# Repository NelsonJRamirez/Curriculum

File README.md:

PROYECTOS MECÁNICOS, ESTRUCTURALES Y ELECTRÓNICOS DESTACADOS

Esta carpeta reúne algunos de los proyectos más interesantes que he desarrollado en diferentes áreas,
incluyendo diseño mecánico, estructuras metálicas, modelado en SolidWorks, fabricación industrial, proyectos
electrónicos, programación, monitoreo y automatización.

El objetivo de esta sección es mostrar una parte de mi experiencia práctica trabajando con soluciones reales,
tanto en el área mecánica como en el área electrónica. Aquí se incluyen proyectos relacionados con diseño de piezas,
planos, ensambles, estructuras, escaleras industriales, moldes, filtros, sistemas de monitoreo, proyectos con microcontroladores,
aplicaciones, FPGA, STM32, automatización y otros trabajos técnicos desarrollados durante mi formación y experiencia profesional.

Mi participación en estos proyectos ha incluido levantamiento de información, modelado 3D, diseño de componentes,
elaboración de planos, organización de archivos técnicos, desarrollo electrónico, programación, pruebas, documentación
y mejora de soluciones según la necesidad de cada caso.

Estos proyectos representan una muestra de las distintas áreas en las que he trabajado y aprendido.
Algunos están enfocados en fabricación mecánica e industrial, otros en estructuras y otros en electrónica
aplicada. En conjunto, reflejan mi interés por crear soluciones funcionales, entender los sistemas desde su
diseño hasta su aplicación real, y seguir creciendo como profesional en el área técnica.

COPYRIGHT Y USO DEL CONTENIDO

Todo el contenido presentado en esta carpeta pertenece a sus respectivos proyectos y se muestra únicamente
con fines de portafolio, documentación profesional y demostración de experiencia técnica.

No está permitido copiar, reutilizar, modificar, distribuir, vender, publicar, fabricar, redibujar o
utilizar total o parcialmente las imágenes, planos, modelos 3D, códigos, documentos técnicos, diseños,
esquemas, archivos electrónicos, programas, renders o cualquier otro material incluido en esta carpeta
sin autorización previa y por escrito de Nelson J. Ramirez, Equiprec y/o las partes correspondientes según aplique.

La publicación de estos archivos en GitHub no representa una cesión de derechos ni una autorización para
uso comercial, académico, técnico, industrial o personal. El contenido se muestra como evidencia de
experiencia profesional y no debe ser utilizado para reproducción, fabricación, desarrollo de productos derivados o implementación sin autorización.

Algunos proyectos pueden estar resumidos, incompletos o mostrar solo una parte del trabajo realizado, por lo que no deben considerarse como documentación completa de fabricación, instalación, programación o ejecución.

Cualquier uso no autorizado de este material queda estrictamente prohibido.

© 2026 Equiprec / Nelson J. Ramirez. Todos los derechos reservados.

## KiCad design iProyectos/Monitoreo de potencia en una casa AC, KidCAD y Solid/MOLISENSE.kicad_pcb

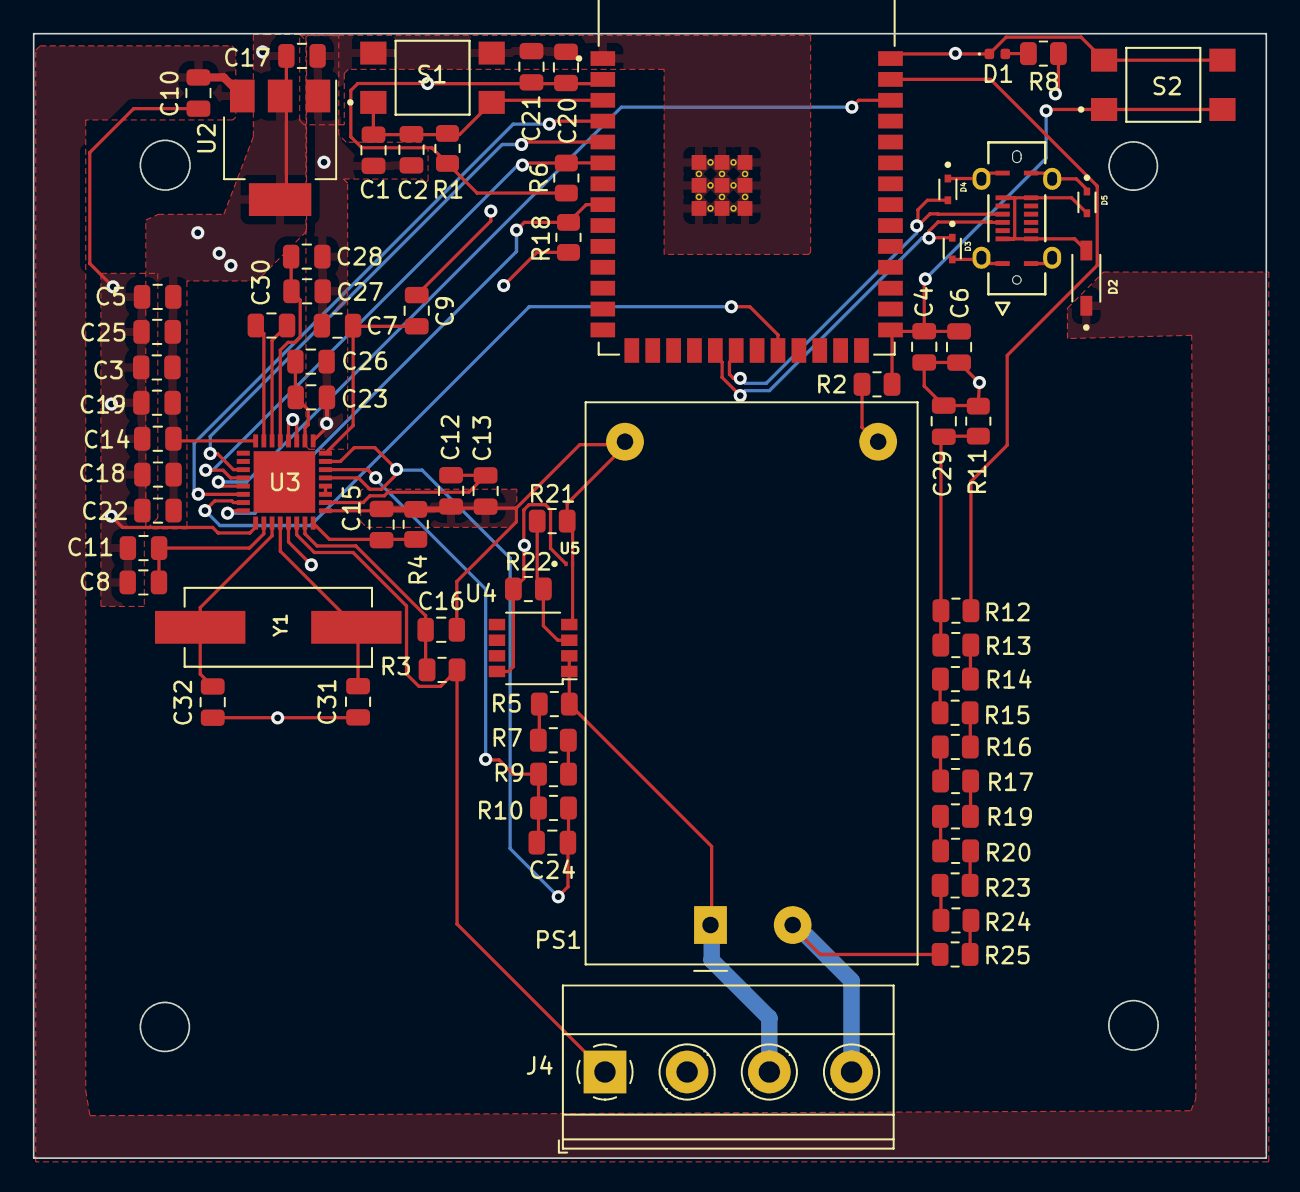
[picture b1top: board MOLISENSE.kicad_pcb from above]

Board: 4 copper layers, 75.0 x 68.4 mm, 73 parts (0 on the bottom side), 46 nets.

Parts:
C1, C4, C29: 1uF; C_0805_2012Metric
C2, C5, C6, C14: 0.1uF; C_0805_2012Metric
C3: 22uF; C_0805_2012Metric
C7, C11, C13, C15, C16, C19, C25, C26, C28: 0.1 uF; C_0805_2012Metric
C8, C9, C12, C18, C22, C23, C27: 4.7 uF; C_0805_2012Metric
C10, C17, C20, C21: C 10uF; C_0805_2012Metric
C24: 15nF; C_0805_2012Metric
C30: 0.47uF; C_0805_2012Metric
C31, C32: 22Pf; C_0805_2012Metric
D1: LED; LED_0402_1005Metric
D2: 1N5819HW-7-F; SOD3715X145N
D3, D4, D5: LESD5D5.0CT1G; TVS_LESD5D5.0CT1G
J3: 2171820001; MOLEX_2171820001
J4: Screw_Terminal_01x04; TerminalBlock_Phoenix_MKDS-1,5-4_1x04_P5.00mm_Horizontal
PS1: HLK-PM03; Converter_ACDC_HiLink_HLK-PMxx
R1, R2: 10K; R_0805_2012Metric
R3, R4: 150k; R_0805_2012Metric
R5, R7, R9: 330k; R_0805_2012Metric
R6, R12, R18, R21, R22: 10k; R_0805_2012Metric
R8: 5.1k; R_0805_2012Metric
R10: 1K; R_0805_2012Metric
R11: 1k; R_0805_2012Metric
R13, R14, R15, R16, R17, R19, R20, R23, R24, R25: 100k; R_0805_2012Metric
S1, S2: TL3305AF160QG; SW_TL3305AF160QG
U1: ESP32-S3-WROOM-1-N8R8; XCVR_ESP32S3WROOM1N8R8
U2: AMS1117-3.3; SOT-223-3_TabPin2
U3: QFN50P500X500X80-33N
U4: LM358; SuperSOT-8
U5: DIO_PESD5V0R1BSFYL
Y1: ECS-120-32-5PX-TR; XTAL_ECS-120-32-5PX-TR

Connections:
+3.3V: C3.1, C5.1, C14.1, C17.1, C18.1, C19.1, C20.1, C21.1, C22.1, C25.1, PS1.4 (+Vout), R1.1, R2.1, R6.1, R8.2, R18.2, R22.1, U1.2 (3V3), U2.2 (VO), U3.5 (VDD), U3.24 (VDD_2), U4.8 (V+), U5.1
+5V: C10.1, D2.C, U2.3 (VI)
/Fases: J4.4, PS1.2 (AC/N), R25.1
/NEUTRO: J4.3, PS1.1 (AC/L), R5.1, U4.1, U4.2 (-)
D+: D3.1, J3.A6 (DP1), U1.19 (IO11)
D-: D4.2, J3.A7 (DN1), U1.20 (IO12)
EN: C1.2, C2.1, R1.2, S1.1, S1.2, U1.3 (EN)
GND: C1.1, C2.2, C3.2, C4.1, C5.2, C6.2, C7.1, C8.2, C9.1, C10.2, C11.2, C12.2, C13.2, C14.2, C15.2, C16.1, C17.2, C18.2, C19.2, C20.2, C21.2, C22.2, C23.2, C25.2, C26.2, C27.2, C28.2, C29.2, C31.2, C32.2, D1.1 (K), D3.2, D4.1, D5.1, J3.A1 (GND1), J3.A12 (GND2), J3.B1 (GND3), J3.B12 (GND4), J3.SH1 (SHIELD1), J3.SH2 (SHIELD2), J3.SH3 (SHIELD3), J3.SH4 (SHIELD4), J4.2, PS1.3 (-Vout), R4.1, R11.2, R21.2, S1.3, S1.4, S2.3, S2.4, U1.1 (GND), U1.40 (GND), U1.41_1 (GND), U1.41_2 (GND), U1.41_3 (GND), U1.41_4 (GND), U1.41_5 (GND), U1.41_6 (GND), U1.41_7 (GND), U1.41_8 (GND), U1.41_9 (GND), U1.41_10, U1.41_11, U1.41_12, U1.41_13, U1.41_14, U1.41_15, U1.41_16, U1.41_17, U1.41_18, U1.41_19, U1.41_20, U1.41_21, U2.1 (GND), U3.1 (DGND), U3.9 (AGND), U3.17 (AGND_2), U3.19 (IBMS), U3.20 (DGND_2), U4.4 (V-), U5.2
GPIO0: C4.2, C6.1, R2.2, S2.1, S2.2, U1.27 (IO0)
unnamed: D1.2 (A), R8.1
unnamed: D2.A, D5.2, J3.A4 (VBUS1), J3.A9 (VBUS2), J3.B4 (VBUS3), J3.B9 (VBUS4)
unnamed: J4.1, R3.1, U3.6 (IAMS)
unnamed: R5.2, R7.1
unnamed: R7.2, R9.1
unnamed: R13.1, R14.2
unnamed: R14.1, R15.2
unnamed: R15.1, R16.2
unnamed: R16.1, R17.2
unnamed: R17.1, R19.2
unnamed: R19.1, R20.2
unnamed: R20.1, R23.2
unnamed: R23.1, R24.2
unnamed: R24.1, R25.2
unnamed: C7.2, C9.2, U3.16 (AVDDOUT)
unnamed: C31.1, U3.4 (CLKIN), Y1.2
unnamed: C32.1, U3.3 (CLKOUT), Y1.1
unnamed: C8.1, C11.1, U3.2 (DVDDOUT)
unnamed: C30.2, U3.23 (FA0)
unnamed: C30.1, U3.22 (FA1)
unnamed: C16.2, R3.2, U3.7 (IAN)
unnamed: C15.1, R4.2, U3.8 (IAP)
unnamed: U3.11 (IBN), U3.12 (IBP)
unnamed: C27.1, C28.1, U3.21 (MSH)
unnamed: C23.1, C26.1, U3.18 (REFIN)
unnamed: C24.1, R10.1, U3.13 (VAMS), U3.15 (VAN)
unnamed: C24.2, R9.2, R10.2, U3.14 (VAP)
unnamed: C12.1, C13.1, U3.10 (VDDOUT2P5)
unnamed: R21.1, R22.2, U4.3 (+)
SCLK: U1.22 (IO14), U3.31 (SCLK)
adc: C29.1, R11.1, R12.1, R13.2
adc_in: R12.2, U1.39 (IO1)
irq_n: U1.5 (IO5), U3.27 (IRQ_N)
misi: U1.38 (IO2), U3.29 (MOSI/RX)
miso: U1.4 (IO4), U3.30 (MISO/TX)
reset: R6.2, U1.6 (IO6), U3.28 (RESET_N)
ss: R18.1, U1.8 (IO15), U3.32 (SS_N)

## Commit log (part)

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2024-05-23 Curriculum
2024-06-01 Datos del proyecto.txt
    Aquí se explica lo principal del proyecto.
